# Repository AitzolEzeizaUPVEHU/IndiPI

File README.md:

# IndiPI
Laboratory kit for Industrial Information Technology based on Raspberry PI 5

## Description
A hands-on educational platform for learning industrial IoT and automation using Raspberry Pi 5.

## Getting Started
The Gerber files are available for creating your own kit. You would need the BOM described, an ADS analog-to-digital converter and a Raspberry PI 5. You can check the figures in order to know how to mount the whole kit.

## Authors
- Imanol Bardaji Zuriarrain
- Aitzol Ezeiza Ramos
- Kauldi Odriozola Ieregi

## License
CC-SA-4.0

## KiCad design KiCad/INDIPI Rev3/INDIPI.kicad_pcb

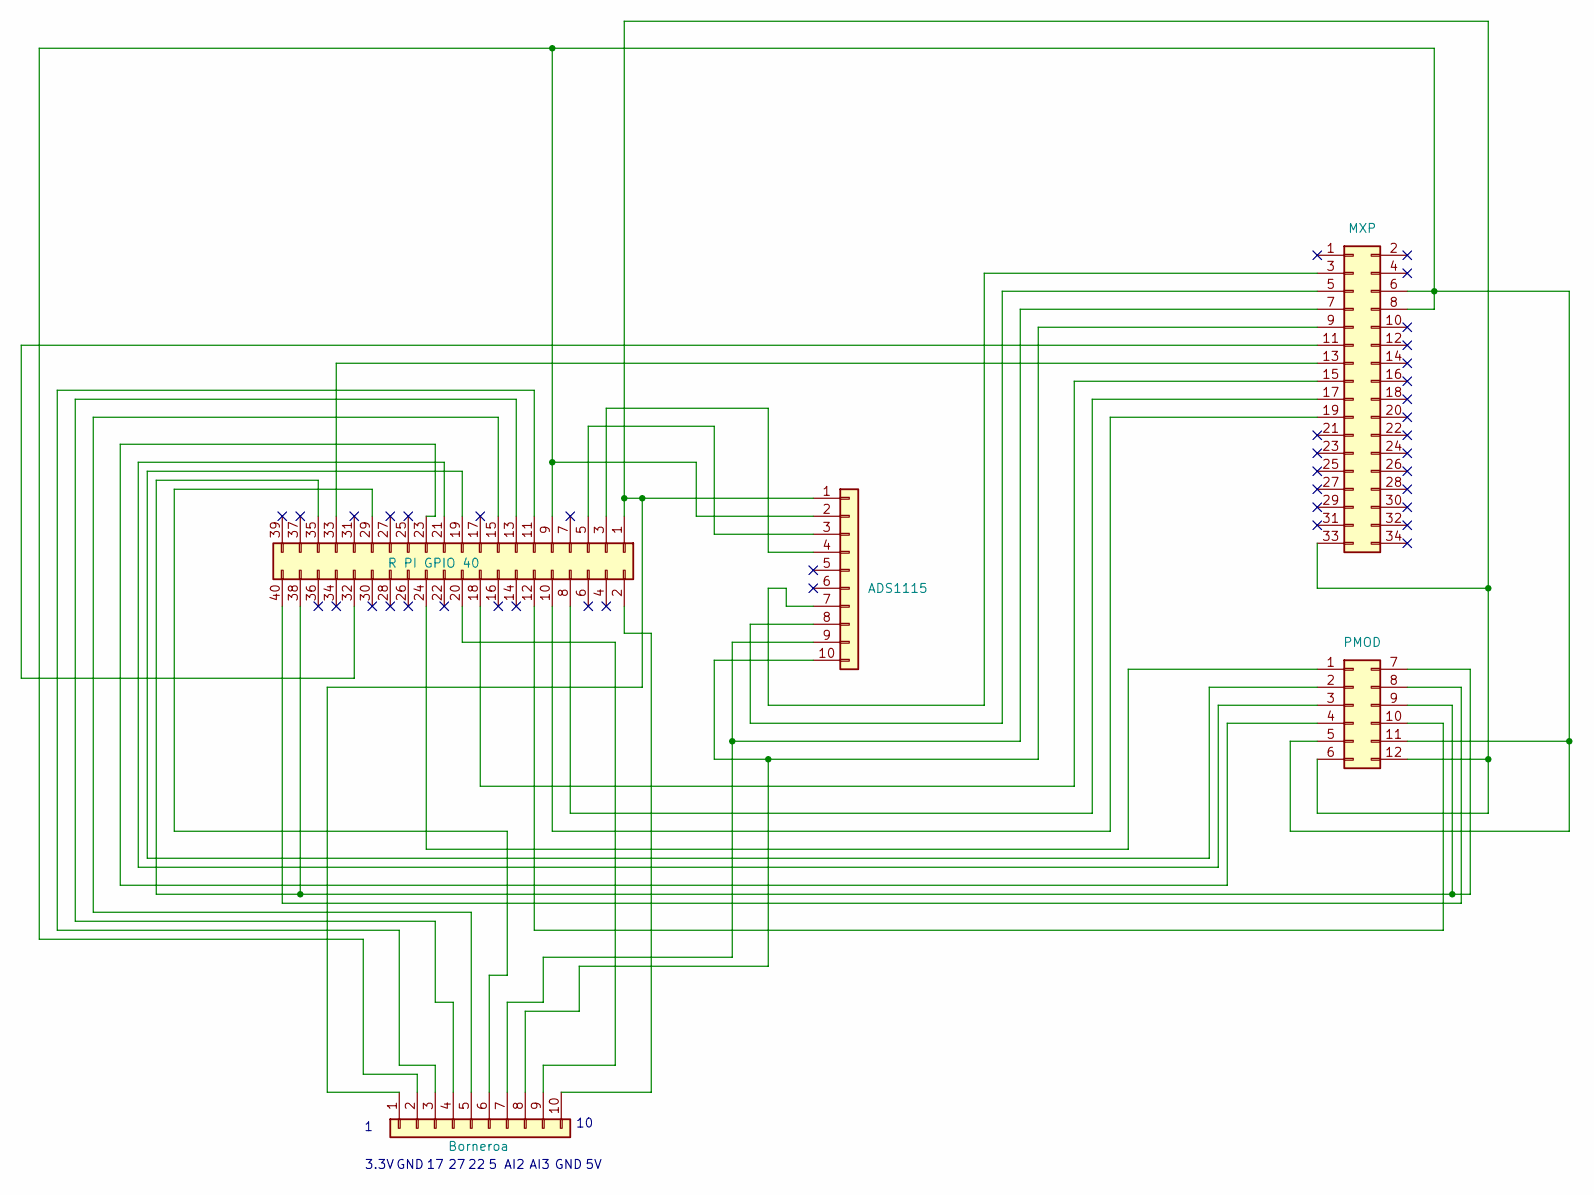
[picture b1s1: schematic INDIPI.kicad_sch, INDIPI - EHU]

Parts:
J1: ADS1115; PinSocket_1x10_P2.54mm_Vertical
J2: R PI GPIO 40; PinHeader_2x20_P2.54mm_Vertical
J3: MXP; PinHeader_2x17_P2.54mm_Horizontal
J4: PMOD; PinHeader_2x06_P2.54mm_Horizontal
J16: Borneroa; PhoenixContact_MSTBVA_2,5_10-G-5,08_1x10_P5.08mm_Vertical

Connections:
unnamed: J1.1, J2.1, J3.33, J4.6, J4.12, J16.1
unnamed: J1.2, J2.9, J3.6, J3.8, J4.5, J4.11, J16.2
unnamed: J1.3, J2.5
unnamed: J1.4, J2.3
unnamed: J1.7, J3.3
unnamed: J1.8, J3.5
unnamed: J1.9, J3.7, J16.7
unnamed: J1.10, J3.9, J16.8
unnamed: J2.8, J3.17
unnamed: J2.10, J3.19
unnamed: J2.12, J4.10
unnamed: J2.18, J3.15
unnamed: J2.19, J4.2
unnamed: J2.21, J4.3
unnamed: J2.23, J4.4
unnamed: J2.24, J4.1
unnamed: J2.32, J3.11
unnamed: J2.33, J3.13
unnamed: J2.35, J2.38, J4.7, J4.9
unnamed: J2.40, J4.8
unnamed: J2.11, J16.3
unnamed: J2.13, J16.4
unnamed: J2.15, J16.5
unnamed: J2.29, J16.6
unnamed: J2.20, J16.9
unnamed: J2.2, J16.10

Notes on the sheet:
AI2
3.3V
AI3
GND
GND

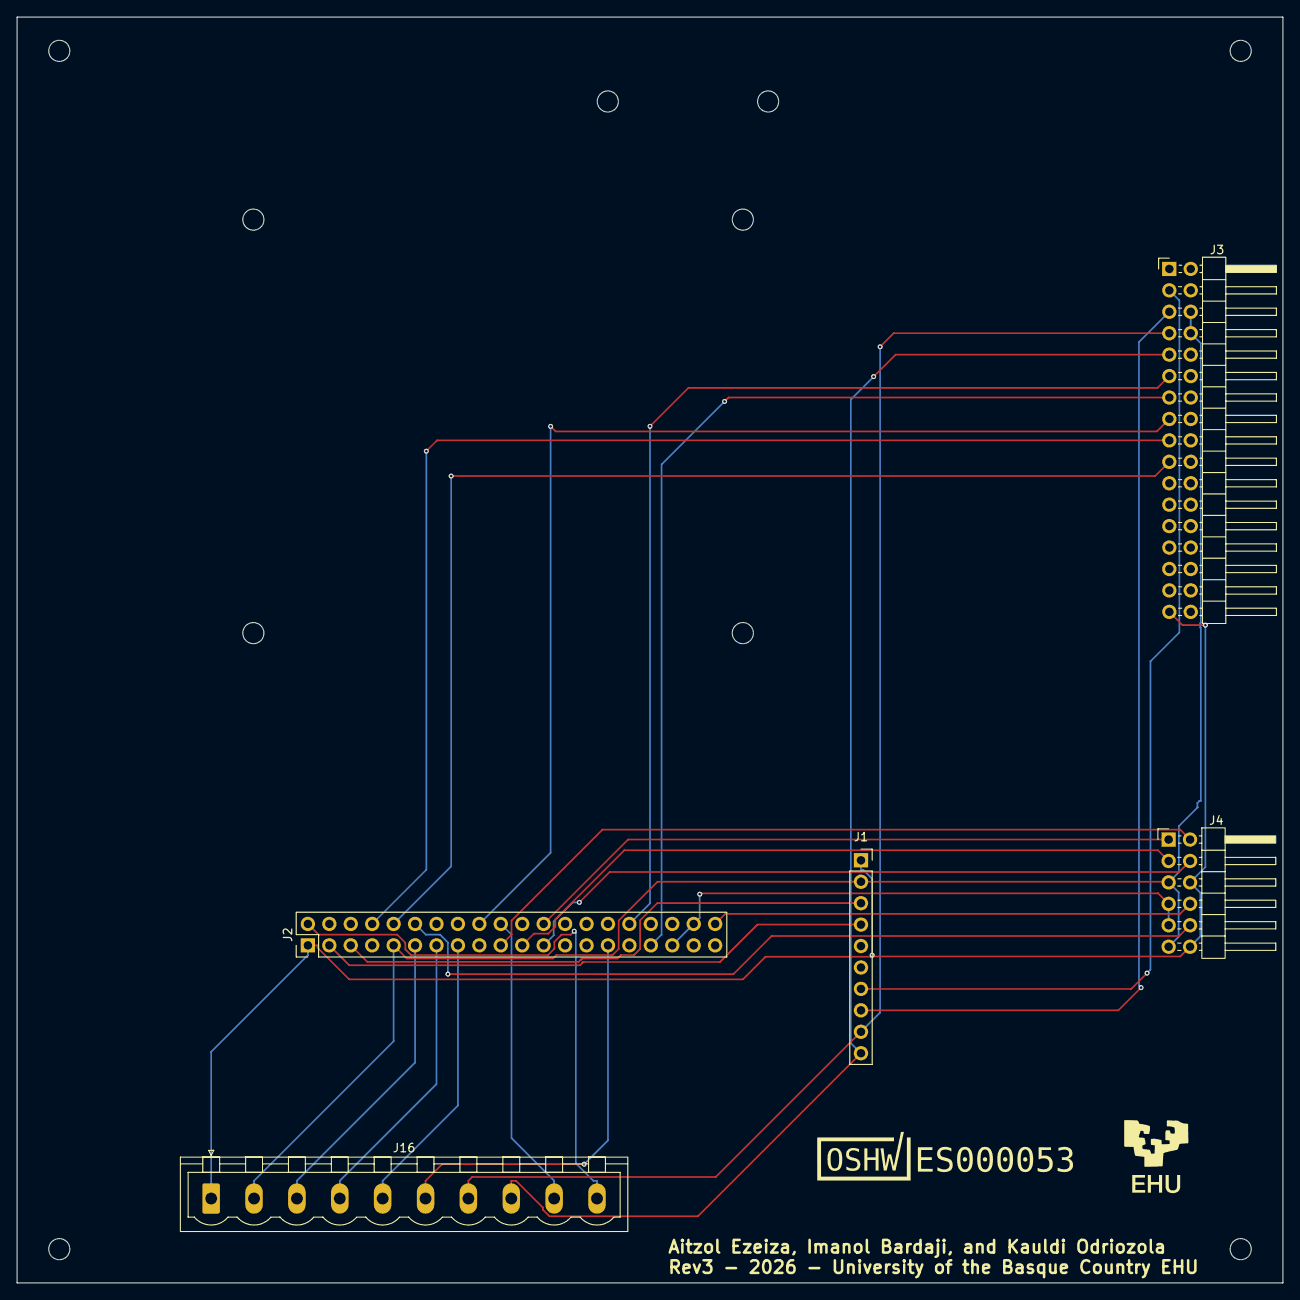
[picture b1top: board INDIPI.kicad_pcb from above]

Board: 2 copper layers, 150.0 x 150.0 mm, 17 parts (0 on the bottom side), 26 nets.

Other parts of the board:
EHU: LOGO; EHU_logotipo.txiki
MH1, MH2, MH3, MH4, MH6, MH7: MountingHole_2.5mm
MHR1, MHR2, MHR3, MHR4: MountingHole_2.5mm
OSHWA: LOGO; OSHWA

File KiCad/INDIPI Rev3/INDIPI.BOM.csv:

"Reference","Qty","Value","DNP","Exclude from BOM","Exclude from Board","Footprint","Datasheet"
"J1","1","ADS1115","","","","Connector_PinSocket_2.54mm:PinSocket_1x10_P2.54mm_Vertical","~"
"J2","1","R PI GPIO 40","","","","Connector_PinHeader_2.54mm:PinHeader_2x20_P2.54mm_Vertical","~"
"J3","1","MXP","","","","Connector_PinHeader_2.54mm:PinHeader_2x17_P2.54mm_Horizontal","~"
"J4","1","PMOD","","","","Connector_PinHeader_2.54mm:PinHeader_2x06_P2.54mm_Horizontal","~"
"J16","1","Borneroa","","","","Connector_Phoenix_MSTB:PhoenixContact_MSTBVA_2,5_10-G-5,08_1x10_P5.08mm_Vertical","~"

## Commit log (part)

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2025-06-26 Rename 1741425425717.jpg to IndiPI photo.jpg
